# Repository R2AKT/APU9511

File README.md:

License addendum - https://github.com/R2AKT/APU9511/blob/main/Addendum.txt
# APU9511

APU (Arithmetic Processing Unit) module for CPU_8080 board based on AM9511/8231.
For Mega-80 (Mega-580) DIY 8-bit micro-computer - https://github.com/R2AKT/Mega-80.

*Note: The processor module CPU_8080 must use a 580VK38 (8238) system bus controller, which is not functional when using 580VK28 (8228).

Status: tested.

Модуль математического процессора на базе AM9511/8231.
Для самодельной 8-битной микро-ЭВМ - https://github.com/R2AKT/Mega-80.

*Примечание: в процессорном модуле CPU_8080 должен применяться контроллер системной шины 580ВК38 (8238), при использовании 580ВК28 (8228) не работоспособно.

Статус: проверено.

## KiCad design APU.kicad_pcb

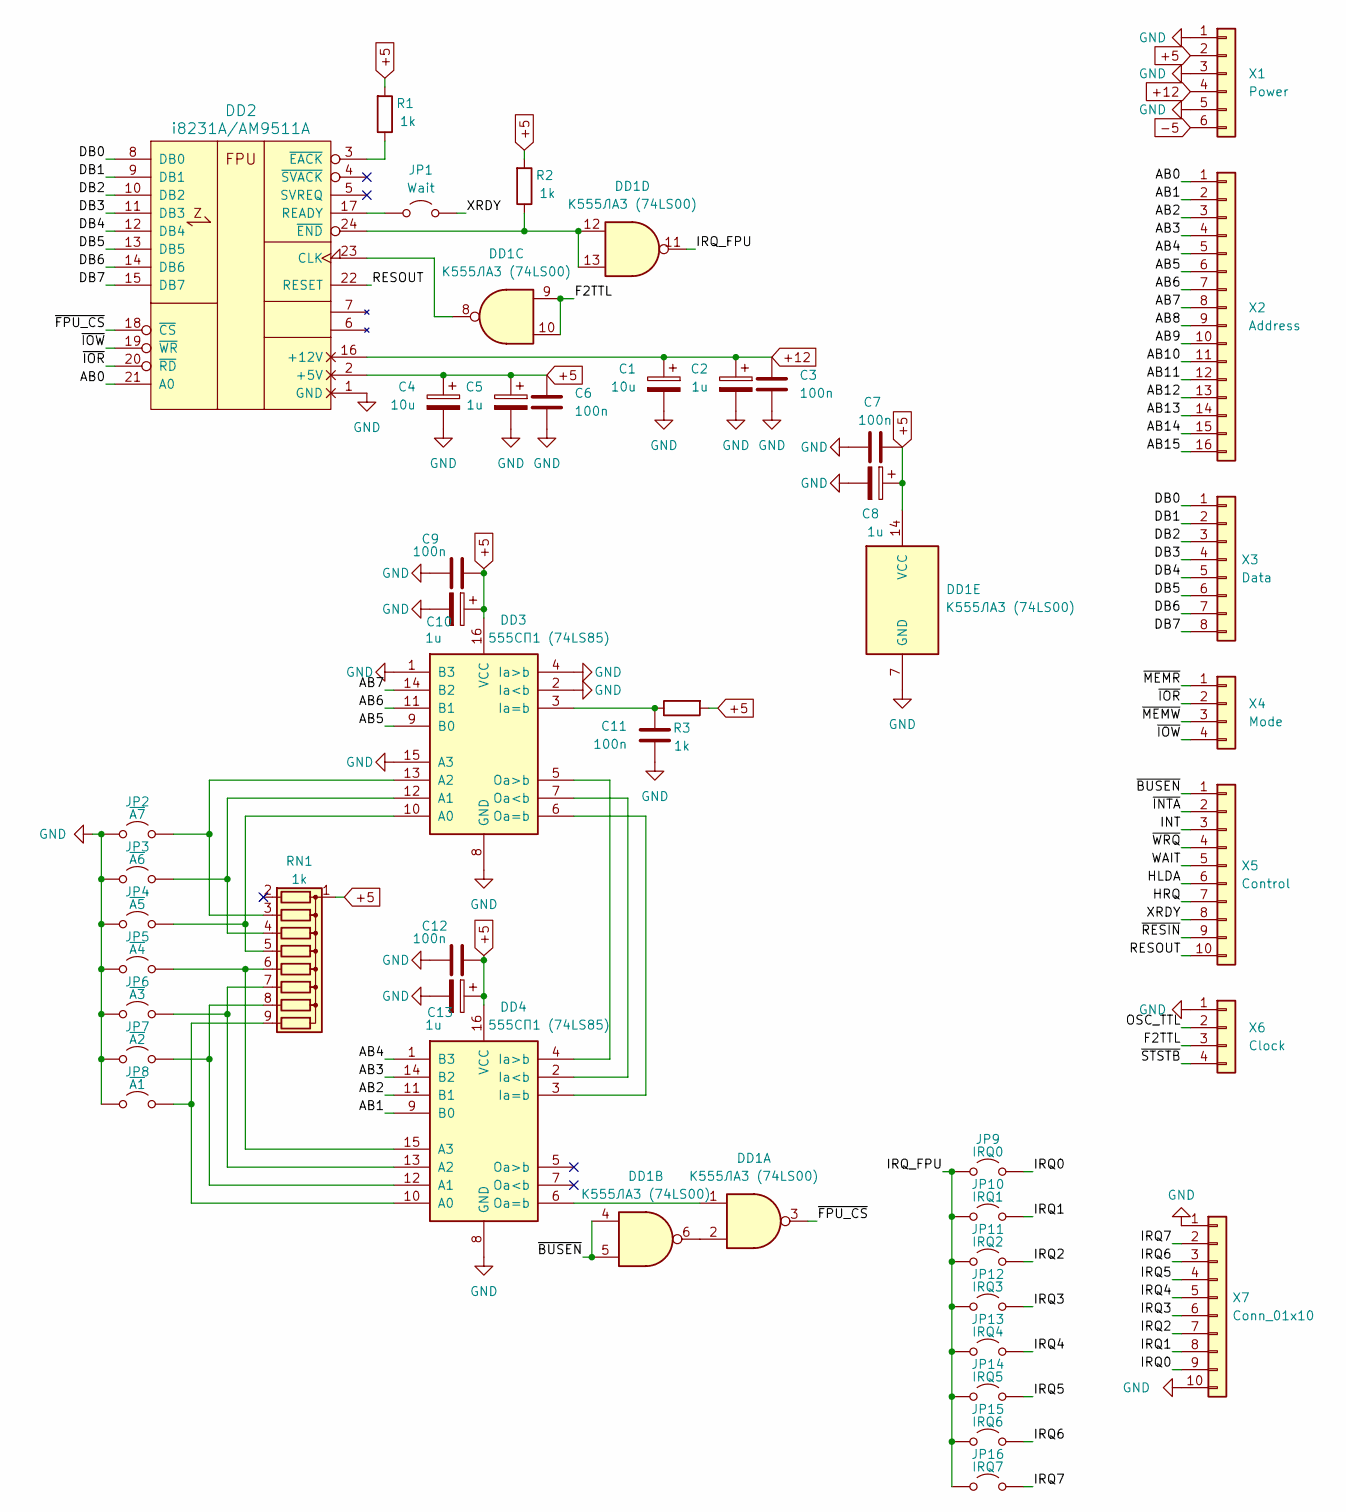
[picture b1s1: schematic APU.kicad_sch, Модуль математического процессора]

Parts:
C1, C4: 10u; CP_EIA-3216-18_Kemet-A_Pad1.58x1.35mm_HandSolder
C2, C5, C8, C10, C13: 1u; CP_EIA-3216-18_Kemet-A_Pad1.58x1.35mm_HandSolder
C3, C6, C7, C9, C11, C12: 100n; C_0805_2012Metric_Pad1.18x1.45mm_HandSolder
DD1: К555ЛА3 (74LS00); DIP-14_W7.62mm_Socket_LongPads
DD2: i8231A/AM9511A; DIP-24_W15.24mm_Socket_LongPads
DD3, DD4: 555СП1 (74LS85); DIP-16_W7.62mm_Socket_LongPads
JP1: Wait; SolderJumper-2_P1.3mm_Open_RoundedPad1.0x1.5mm
JP2: ~{A7}; SolderJumper-2_P1.3mm_Open_RoundedPad1.0x1.5mm
JP3: ~{A6}; SolderJumper-2_P1.3mm_Open_RoundedPad1.0x1.5mm
JP4: ~{A5}; SolderJumper-2_P1.3mm_Open_RoundedPad1.0x1.5mm
JP5: ~{A4}; SolderJumper-2_P1.3mm_Open_RoundedPad1.0x1.5mm
JP6: ~{A3}; SolderJumper-2_P1.3mm_Open_RoundedPad1.0x1.5mm
JP7: ~{A2}; SolderJumper-2_P1.3mm_Open_RoundedPad1.0x1.5mm
JP8: ~{A1}; SolderJumper-2_P1.3mm_Open_RoundedPad1.0x1.5mm
JP9: IRQ0; SolderJumper-2_P1.3mm_Open_RoundedPad1.0x1.5mm
JP10: IRQ1; SolderJumper-2_P1.3mm_Open_RoundedPad1.0x1.5mm
JP11: IRQ2; SolderJumper-2_P1.3mm_Open_RoundedPad1.0x1.5mm
JP12: IRQ3; SolderJumper-2_P1.3mm_Open_RoundedPad1.0x1.5mm
JP13: IRQ4; SolderJumper-2_P1.3mm_Open_RoundedPad1.0x1.5mm
JP14: IRQ5; SolderJumper-2_P1.3mm_Open_RoundedPad1.0x1.5mm
JP15: IRQ6; SolderJumper-2_P1.3mm_Open_RoundedPad1.0x1.5mm
JP16: IRQ7; SolderJumper-2_P1.3mm_Open_RoundedPad1.0x1.5mm
R1, R2, R3: 1k; R_0805_2012Metric_Pad1.20x1.40mm_HandSolder
RN1: 1k; R_Array_SIP9
X1: Power; PinHeader_1x06_P2.54mm_Vertical
X2: Address; PinHeader_1x16_P2.54mm_Vertical
X3: Data; PinHeader_1x08_P2.54mm_Vertical
X4: Mode; PinHeader_1x04_P2.54mm_Vertical
X5: Control; PinHeader_1x10_P2.54mm_Vertical
X6: Clock; PinHeader_1x04_P2.54mm_Vertical
X7: Conn_01x10; PinHeader_1x10_P2.54mm_Vertical

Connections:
+5: C4.1, C5.1, C6.1, C7.1, C8.1, C9.1, C10.1, C12.1, C13.1, DD1.14 (VCC), DD2.2 (+5V), DD3.16 (VCC), DD4.16 (VCC), R1.2, R2.2, R3.2, RN1.1 (common), X1.2
+12: C1.1, C2.1, C3.1, DD2.16 (+12V), X1.4
-5: X1.6
/AB0: DD2.21 (A0), X2.1
/AB1: DD4.9 (B0), X2.2
/AB2: DD4.11 (B1), X2.3
/AB3: DD4.14 (B2), X2.4
/AB4: DD4.1 (B3), X2.5
/AB5: DD3.9 (B0), X2.6
/AB6: DD3.11 (B1), X2.7
/AB7: DD3.14 (B2), X2.8
/AB8: X2.9
/AB9: X2.10
/AB10: X2.11
/AB11: X2.12
/AB12: X2.13
/AB13: X2.14
/AB14: X2.15
/AB15: X2.16
/DB0: DD2.8 (DB0), X3.1
/DB1: DD2.9 (DB1), X3.2
/DB2: DD2.10 (DB2), X3.3
/DB3: DD2.11 (DB3), X3.4
/DB4: DD2.12 (DB4), X3.5
/DB5: DD2.13 (DB5), X3.6
/DB6: DD2.14 (DB6), X3.7
/DB7: DD2.15 (DB7), X3.8
/F2TTL: DD1.9, DD1.10, X6.3
/HLDA: X5.6
/HRQ: X5.7
/INT: X5.3
/IRQ0: JP9.2 (B), X7.9
/IRQ1: JP10.2 (B), X7.8
/IRQ2: JP11.2 (B), X7.7
/IRQ3: JP12.2 (B), X7.6
/IRQ4: JP13.2 (B), X7.5
/IRQ5: JP14.2 (B), X7.4
/IRQ6: JP15.2 (B), X7.3
/IRQ7: JP16.2 (B), X7.2
/IRQ_FPU: DD1.11, JP9.1 (A), JP10.1 (A), JP11.1 (A), JP12.1 (A), JP13.1 (A), JP14.1 (A), JP15.1 (A), JP16.1 (A)
/OSC_TTL: X6.2
/RESOUT: DD2.22 (RESET), X5.10
/WAIT: X5.5
/XRDY: JP1.2 (B), X5.8
/~BUSEN: DD1.4, DD1.5, X5.1
/~FPU_CS: DD1.3, DD2.18 (~CS)
/~INTA: X5.2
/~IOR: DD2.20 (~RD), X4.2
/~IOW: DD2.19 (~WR), X4.4
/~MEMR: X4.1
/~MEMW: X4.3
/~RESIN: X5.9
/~STSTB: X6.4
/~WRQ: X5.4
GND: C1.2, C2.2, C3.2, C4.2, C5.2, C6.2, C7.2, C8.2, C9.2, C10.2, C11.2, C12.2, C13.2, DD1.7 (GND), DD2.1 (GND), DD3.1 (B3), DD3.2 (Ia<b), DD3.4 (Ia>b), DD3.8 (GND), DD3.15 (A3), DD4.8 (GND), JP2.1 (A), JP3.1 (A), JP4.1 (A), JP5.1 (A), JP6.1 (A), JP7.1 (A), JP8.1 (A), X1.1, X1.3, X1.5, X6.1, X7.1, X7.10
unnamed: DD1.2, DD1.6
unnamed: DD1.8, DD2.23 (CLK)
unnamed: DD2.17 (READY), JP1.1 (A)
unnamed: DD2.3 (~EACK), R1.1
unnamed: DD1.12, DD1.13, DD2.24 (~END), R2.1
unnamed: DD3.10 (A0), JP4.2 (B), RN1.5 (R4)
unnamed: DD3.12 (A1), JP3.2 (B), RN1.4 (R3)
unnamed: DD3.13 (A2), JP2.2 (B), RN1.3 (R2)
unnamed: C11.1, DD3.3 (Ia=b), R3.1
unnamed: DD3.7 (Oa<b), DD4.2 (Ia<b)
unnamed: DD3.6 (Oa=b), DD4.3 (Ia=b)
unnamed: DD3.5 (Oa>b), DD4.4 (Ia>b)
unnamed: DD4.10 (A0), JP8.2 (B), RN1.9 (R8)
unnamed: DD4.12 (A1), JP7.2 (B), RN1.8 (R7)
unnamed: DD4.13 (A2), JP6.2 (B), RN1.7 (R6)
unnamed: DD4.15 (A3), JP5.2 (B), RN1.6 (R5)
unnamed: DD1.1, DD4.6 (Oa=b)

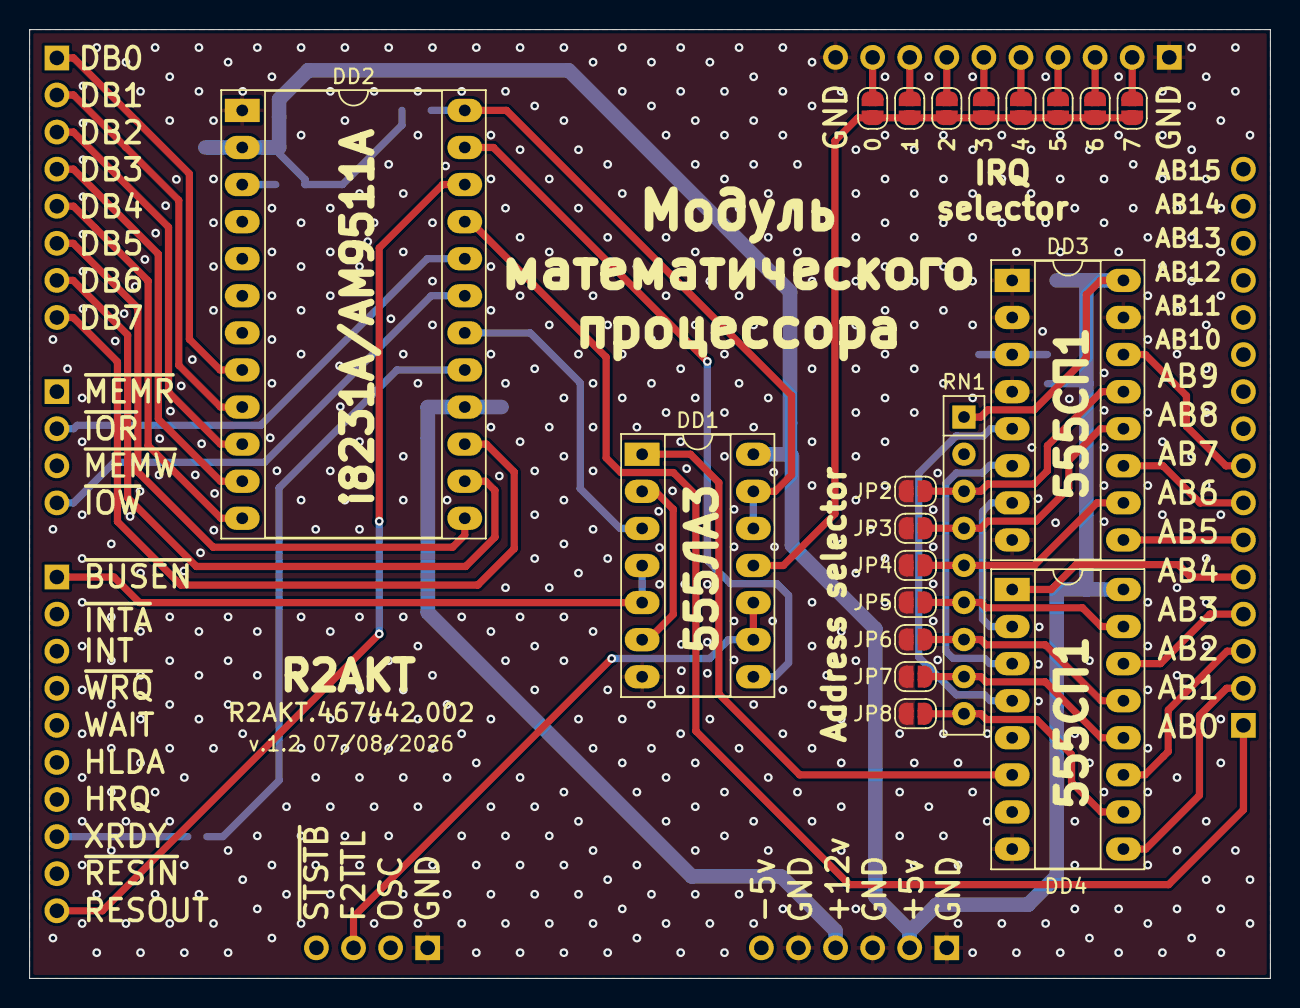
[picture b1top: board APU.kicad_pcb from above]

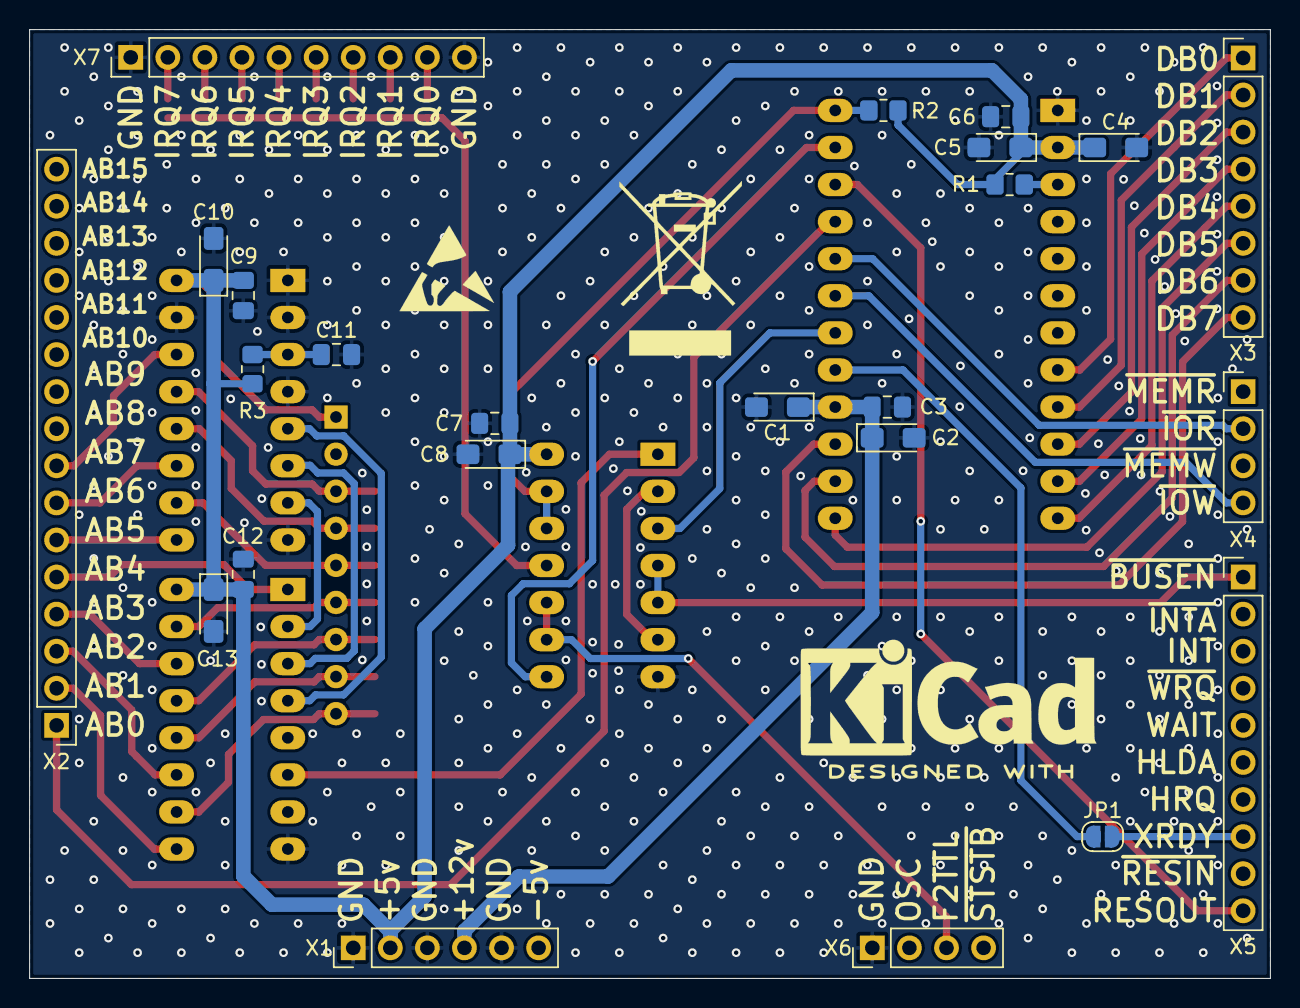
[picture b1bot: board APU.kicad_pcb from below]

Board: 2 copper layers, 85.0 x 65.0 mm, 44 parts (24 on the bottom side), 52 nets.

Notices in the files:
README.md:
License: MIT
